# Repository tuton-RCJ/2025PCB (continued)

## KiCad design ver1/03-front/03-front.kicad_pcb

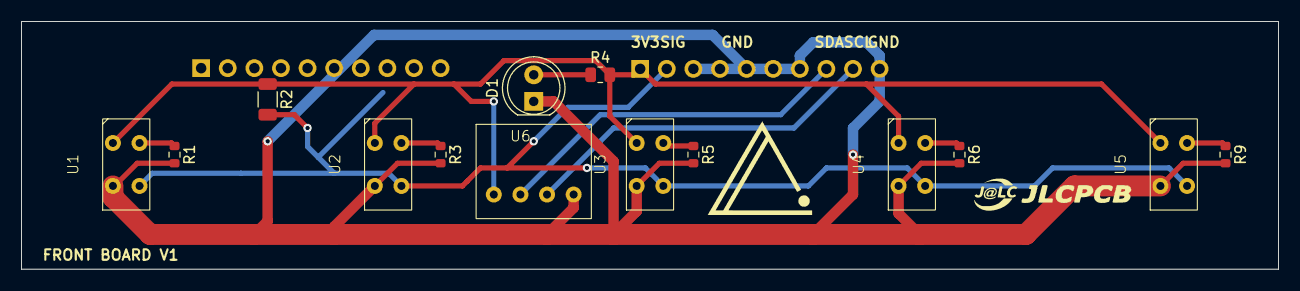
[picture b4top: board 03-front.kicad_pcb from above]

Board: 2 copper layers, 120.0 x 23.7 mm, 15 parts (1 on the bottom side), 11 nets.

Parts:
D1: LED; LED_D5.0mm
J1: Conn_01x10; PinHeader_1x10_P2.54mm_Horizontal
R1, R3, R5, R6, R9: 105; R_0603_1608Metric
R2: 1k; R_1206_3216Metric
R4: 100; R_0805_2012Metric
U1, U2, U3, U4, U5: LBR127HLD
U6: S11059

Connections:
+3V3: J1.1, R2.1, R4.2, U1.1 (Anode), U2.1 (Anode), U3.1 (Anode), U4.1 (Anode), U5.1 (Anode), U6.1 (+V)
GND: D1.1 (K), J1.3, J1.4, J1.5, J1.6, J1.7, J1.10, R1.2, R3.2, R5.2, R6.2, R9.2, U1.3 (Emitter), U2.3 (Emitter), U3.3 (Emitter), U4.3 (Emitter), U5.3 (Emitter), U6.4 (GND)
unnamed: D1.2 (A), R4.1
unnamed: R1.1, U1.2 (Cathode)
unnamed: R3.1, U2.2 (Cathode)
unnamed: R5.1, U3.2 (Cathode)
unnamed: R6.1, U4.2 (Cathode)
unnamed: R9.1, U5.2 (Cathode)
SCL: J1.9, U6.3 (SCL)
SDA: J1.8, U6.2 (SDA)
photo1: J1.2, R2.2, U1.4 (Collector), U2.4 (Collector), U3.4 (Collector), U4.4 (Collector), U5.4 (Collector)

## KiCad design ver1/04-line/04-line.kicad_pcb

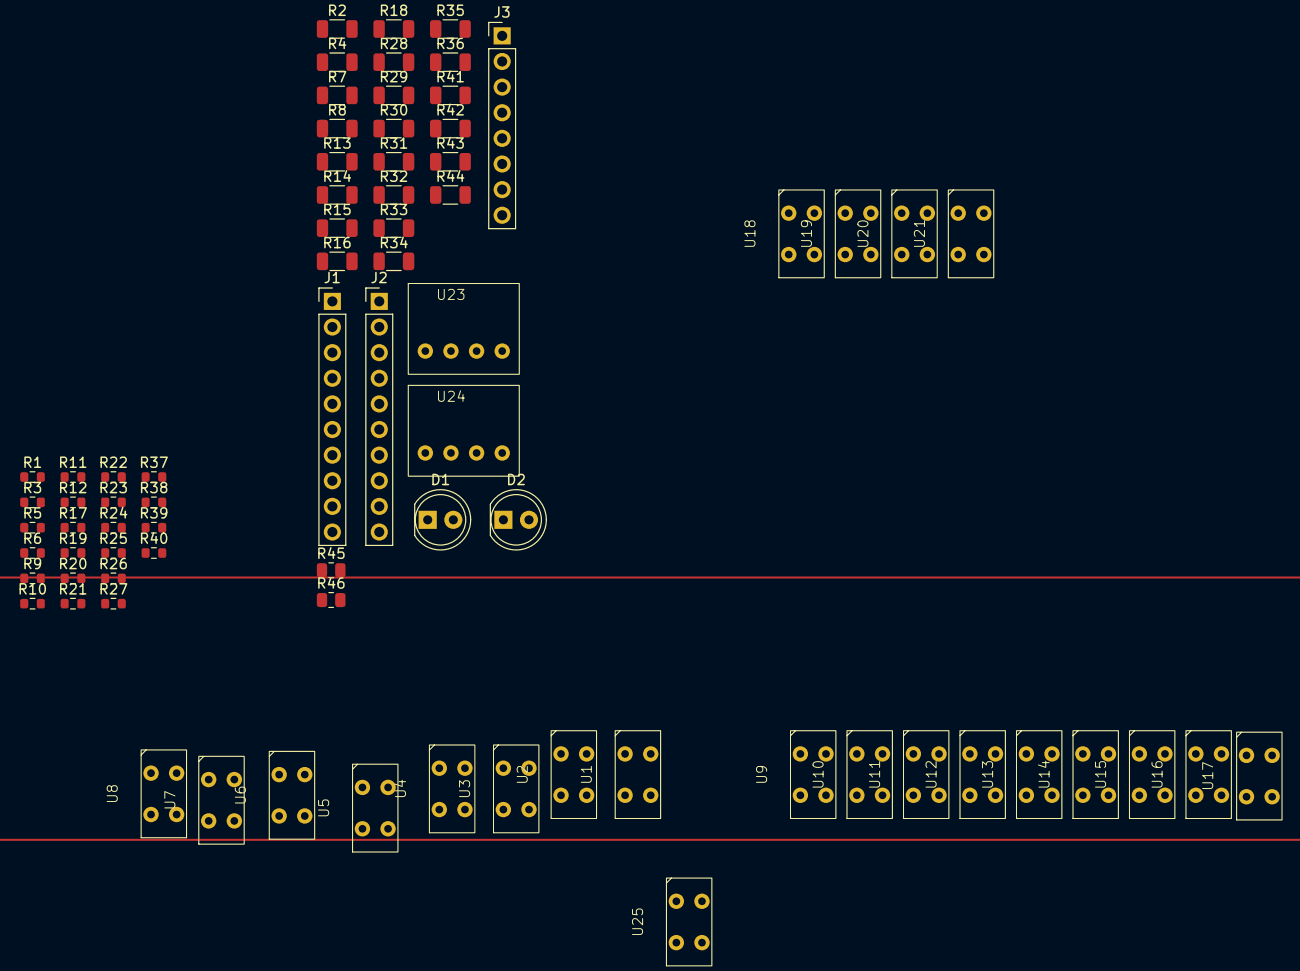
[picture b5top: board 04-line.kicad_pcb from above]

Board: 2 copper layers, 75 parts (0 on the bottom side), 52 nets, no tracks yet.

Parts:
D1, D2: LED; LED_D5.0mm
J1, J2: Conn_01x10; PinHeader_1x10_P2.54mm_Vertical
J3: Conn_01x08; PinHeader_1x08_P2.54mm_Vertical
R1, R3, R5, R6, R9, R10, R11, R12, R17, R19, R20, R21, R22, R23, R24, R25, R26, R27, R37, R38, R39, R40: 105; R_0603_1608Metric
R2, R4, R7, R8, R13, R14, R15, R16, R18, R28, R29, R30, R31, R32, R33, R34, R35, R36, R41, R42, R43, R44: 1k; R_1206_3216Metric
R45, R46: 100; R_0805_2012Metric
U1, U2, U3, U4, U5, U6, U7, U8, U9, U10, U11, U12, U13, U14, U15, U16, U17, U18, U19, U20, U21, U25: LBR127HLD
U23, U24: S11059

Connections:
+3V3: J3.3, R2.1, R4.1, R7.1, R8.1, R13.1, R14.1, R15.1, R16.1, R18.1, R28.1, R29.1, R30.1, R31.1, R32.1, R33.1, R34.1, R35.1, R36.1, R41.1, R42.1, R43.1, R44.1, R45.1, R46.1, U1.1 (Anode), U2.1 (Anode), U3.1 (Anode), U4.1 (Anode), U5.1 (Anode), U6.1 (Anode), U7.1 (Anode), U8.1 (Anode), U9.1 (Anode), U10.1 (Anode), U11.1 (Anode), U12.1 (Anode), U13.1 (Anode), U14.1 (Anode), U15.1 (Anode), U16.1 (Anode), U17.1 (Anode), U18.1 (Anode), U19.1 (Anode), U20.1 (Anode), U21.1 (Anode), U23.1 (+V), U24.1 (+V), U25.1 (Anode)
GND: D1.1 (K), D2.1 (K), J3.6, R1.2, R3.2, R5.2, R6.2, R9.2, R10.2, R11.2, R12.2, R17.2, R19.2, R20.2, R21.2, R22.2, R23.2, R24.2, R25.2, R26.2, R27.2, R37.2, R38.2, R39.2, R40.2, U1.3 (Emitter), U2.3 (Emitter), U3.3 (Emitter), U4.3 (Emitter), U5.3 (Emitter), U6.3 (Emitter), U7.3 (Emitter), U8.3 (Emitter), U9.3 (Emitter), U10.3 (Emitter), U11.3 (Emitter), U12.3 (Emitter), U13.3 (Emitter), U14.3 (Emitter), U15.3 (Emitter), U16.3 (Emitter), U17.3 (Emitter), U18.3 (Emitter), U19.3 (Emitter), U20.3 (Emitter), U21.3 (Emitter), U23.4 (GND), U24.4 (GND), U25.3 (Emitter)
I2C1_SCL: J3.8, U23.3 (SCL)
I2C1_SDA: J3.7, U23.2 (SDA)
I2C2_SCL: J3.2, U24.3 (SCL)
I2C2_SDA: J3.1, U24.2 (SDA)
unnamed: D1.2 (A), R45.2
unnamed: D2.2 (A), R46.2
unnamed: R3.1, U1.2 (Cathode)
unnamed: R5.1, U2.2 (Cathode)
unnamed: R6.1, U3.2 (Cathode)
unnamed: R9.1, U4.2 (Cathode)
unnamed: R10.1, U5.2 (Cathode)
unnamed: R11.1, U6.2 (Cathode)
unnamed: R12.1, U7.2 (Cathode)
unnamed: R17.1, U8.2 (Cathode)
unnamed: R19.1, U9.2 (Cathode)
unnamed: R20.1, U10.2 (Cathode)
unnamed: R21.1, U11.2 (Cathode)
unnamed: R22.1, U12.2 (Cathode)
unnamed: R23.1, U13.2 (Cathode)
unnamed: R24.1, U14.2 (Cathode)
unnamed: R25.1, U15.2 (Cathode)
unnamed: R26.1, U16.2 (Cathode)
unnamed: R27.1, U17.2 (Cathode)
unnamed: R37.1, U18.2 (Cathode)
unnamed: R38.1, U19.2 (Cathode)
unnamed: R39.1, U20.2 (Cathode)
unnamed: R40.1, U21.2 (Cathode)
unnamed: R1.1, U25.2 (Cathode)
photo_LL: J1.10, R43.2, U20.4 (Collector)
photo_L_1: J1.1, R2.2, U25.4 (Collector)
photo_L_2: J1.2, R4.2, U1.4 (Collector)
photo_L_3: J1.3, R7.2, U2.4 (Collector)
photo_L_4: J1.4, R8.2, U3.4 (Collector)
photo_L_5: J1.5, R13.2, U4.4 (Collector)
photo_L_6: J1.6, R14.2, U5.4 (Collector)
photo_L_7: J1.7, R15.2, U6.4 (Collector)
photo_L_8: J1.8, R16.2, U7.4 (Collector)
photo_L_9: J1.9, R18.2, U8.4 (Collector)
photo_RR: J2.10, R44.2, U21.4 (Collector)
photo_R_1: J2.1, R28.2, U9.4 (Collector)
photo_R_2: J2.2, R29.2, U10.4 (Collector)
photo_R_3: J2.3, R30.2, U11.4 (Collector)
photo_R_4: J2.4, R31.2, U12.4 (Collector)
photo_R_5: J2.5, R32.2, U13.4 (Collector)
photo_R_6: J2.6, R33.2, U14.4 (Collector)
photo_R_7: J2.7, R34.2, U15.4 (Collector)
photo_R_8: J2.8, R35.2, U16.4 (Collector)
photo_R_9: J2.9, R36.2, U17.4 (Collector)
photo_center: J3.4, R41.2, U18.4 (Collector)
photo_front: J3.5, R42.2, U19.4 (Collector)
